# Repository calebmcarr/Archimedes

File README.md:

# Archimedes
Software Interface for the Spatial Interference Mitigation Circuit

## Getting started
These instructions will get a working copy of the project on your local machine.
### Prerequisites
What you'll need:
1. Matlab
2. Installed Hardware (read the User Manual for more detail)

Once you have these, progress to install and test run
## Installing and Running Interface
1. clone the repository
```
git clone https://github/calebmcarr/Archimedes
```
2. Open Matlab
3. cd to the Archimedes repo in Matlab terminal
```
cd ./Archimedes
```

4. Run simc_interface.mlapp in Matlab terminal
```
simc_interface
```

## Authors
* **[Caleb Carr](https://calebmcarr.github.io)** - Programmer and Documentation Author
## License
This project is licensed under the GNU GPL v3.  Can be viewed at [LICENSE.txt](LICENSE.txt)
## Acknowledgements
* **[Caleb J. Fulton, PhD](http://www.ou.edu/coe/ece/faculty_directory/dr_fulton)** - Project supervisor and advisor
* **Robin Irazoqui, PhD** - Dissertation on SIMC whose work this interface is based around

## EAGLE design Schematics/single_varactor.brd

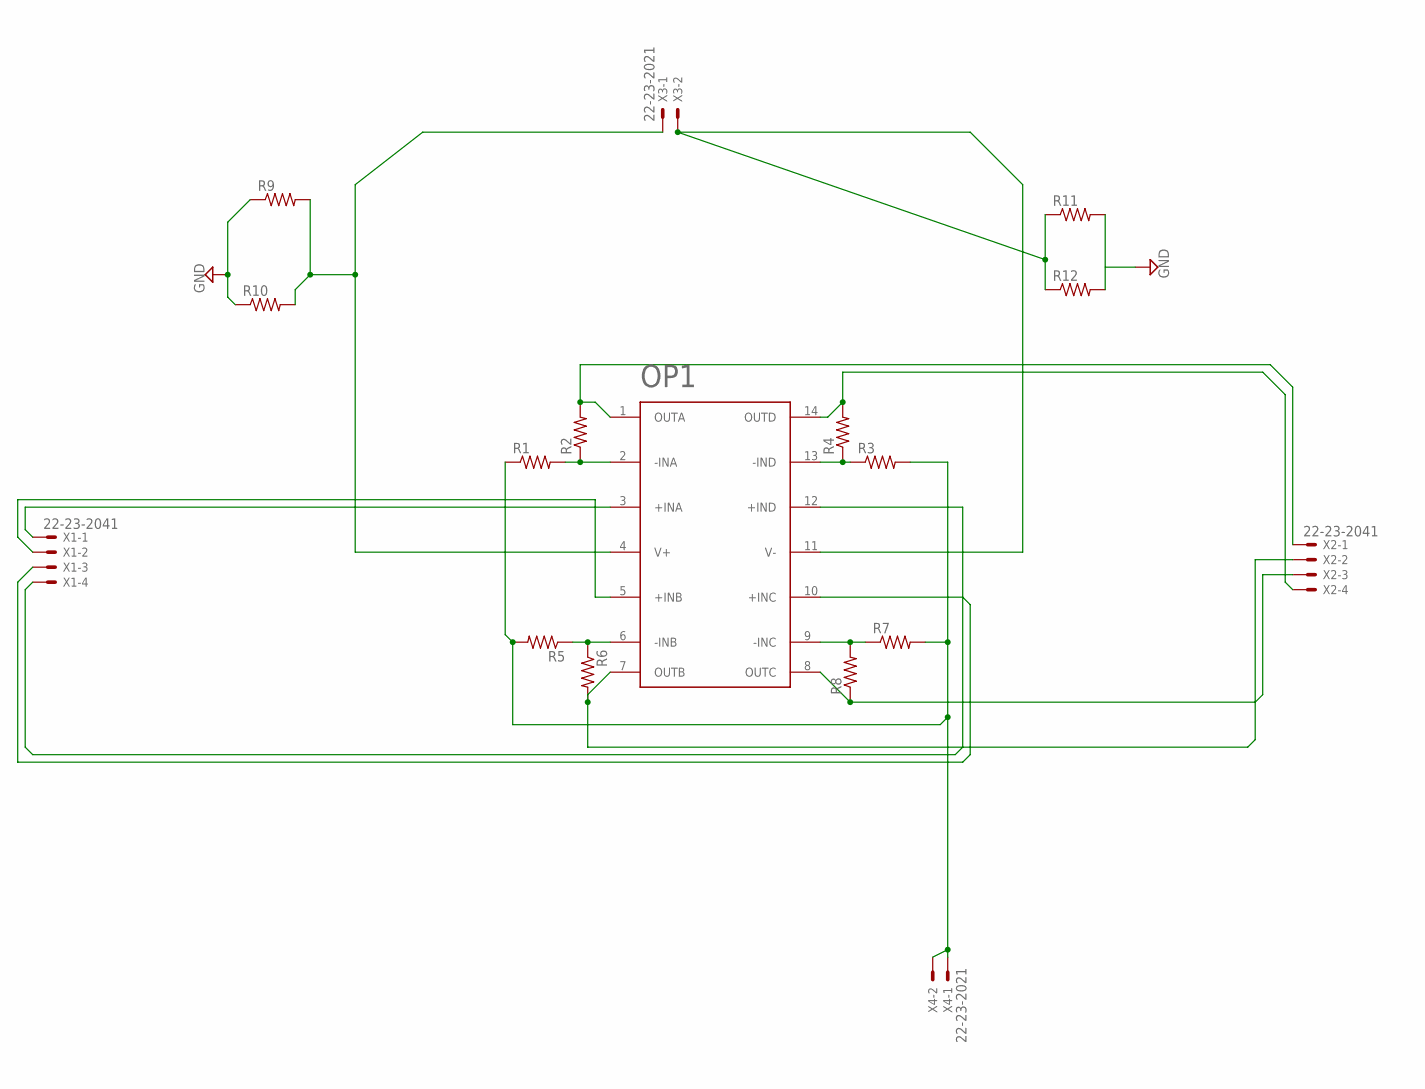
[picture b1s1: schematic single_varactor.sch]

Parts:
OP1: OPAX4172; OPAX172
R1, R2, R3, R4, R5, R6, R7, R8, R9, R10, R11, R12: R-US_0204/2V; 0204V
X1, X2: 22-23-2041
X3, X4: 22-23-2021

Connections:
GND: R9.1, R10.1
unnamed: OP1.2 (-INA), R1.2, R2.1
unnamed: OP1.13 (-IND), R3.1, R4.1
unnamed: OP1.6 (-INB), R5.1, R6.1
unnamed: OP1.9 (-INC), R7.1, R8.2
unnamed: OP1.14 (OUTD), R4.2, X2.4
unnamed: OP1.1 (OUTA), R2.2, X2.1
unnamed: OP1.7 (OUTB), R6.2, X2.2
unnamed: OP1.8 (OUTC), R8.1, X2.3
unnamed: OP1.4 (V+), R9.2, R10.2, X3.1
unnamed: OP1.3 (+INA), X1.1
unnamed: OP1.5 (+INB), X1.2
unnamed: OP1.10 (+INC), X1.3
unnamed: OP1.12 (+IND), X1.4
unnamed: R11.2, R12.2
unnamed: R1.1, R3.2, R5.2, R7.2, X4.1, X4.2
unnamed: OP1.11 (V-), R11.1, R12.1, X3.2

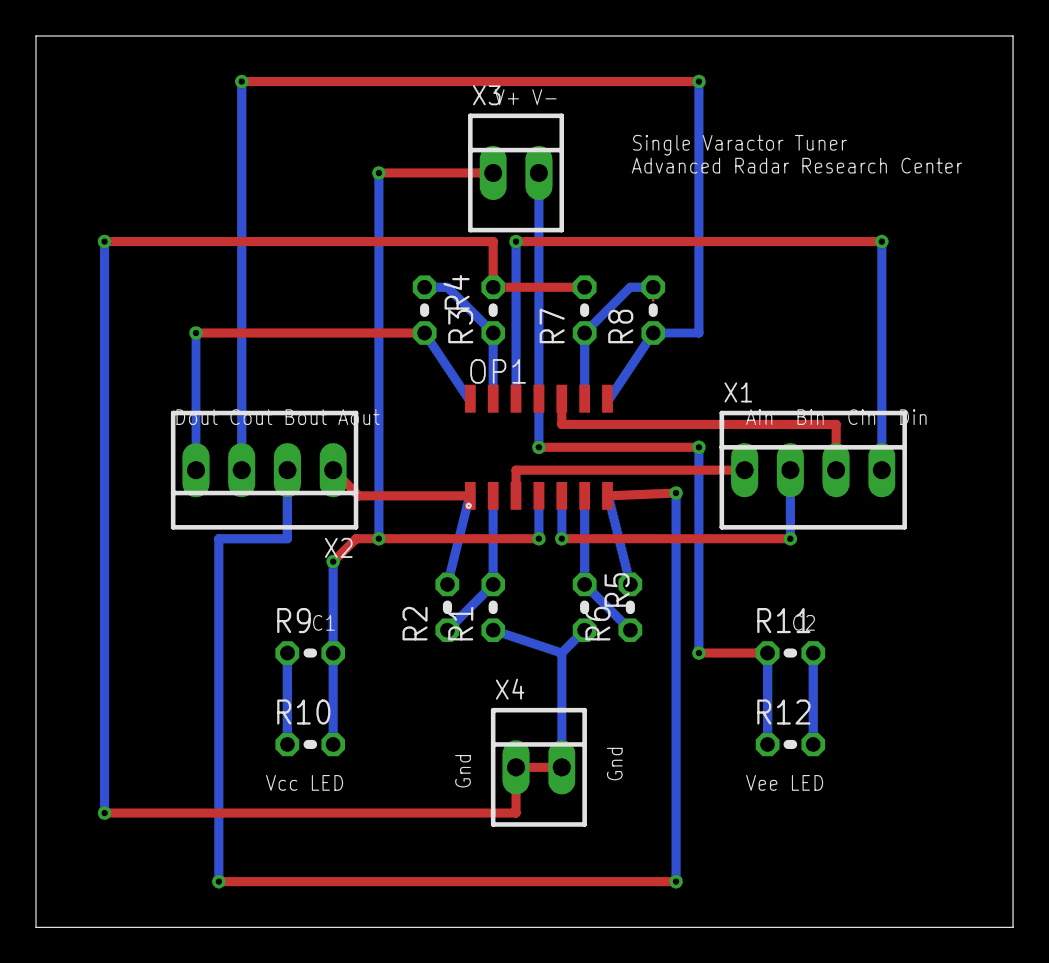
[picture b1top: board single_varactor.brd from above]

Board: 2 copper layers, 54.3 x 49.5 mm, 17 parts (0 on the bottom side), 17 nets.

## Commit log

2019-09-28 Add files via upload
    Initial commit. Still not finished
